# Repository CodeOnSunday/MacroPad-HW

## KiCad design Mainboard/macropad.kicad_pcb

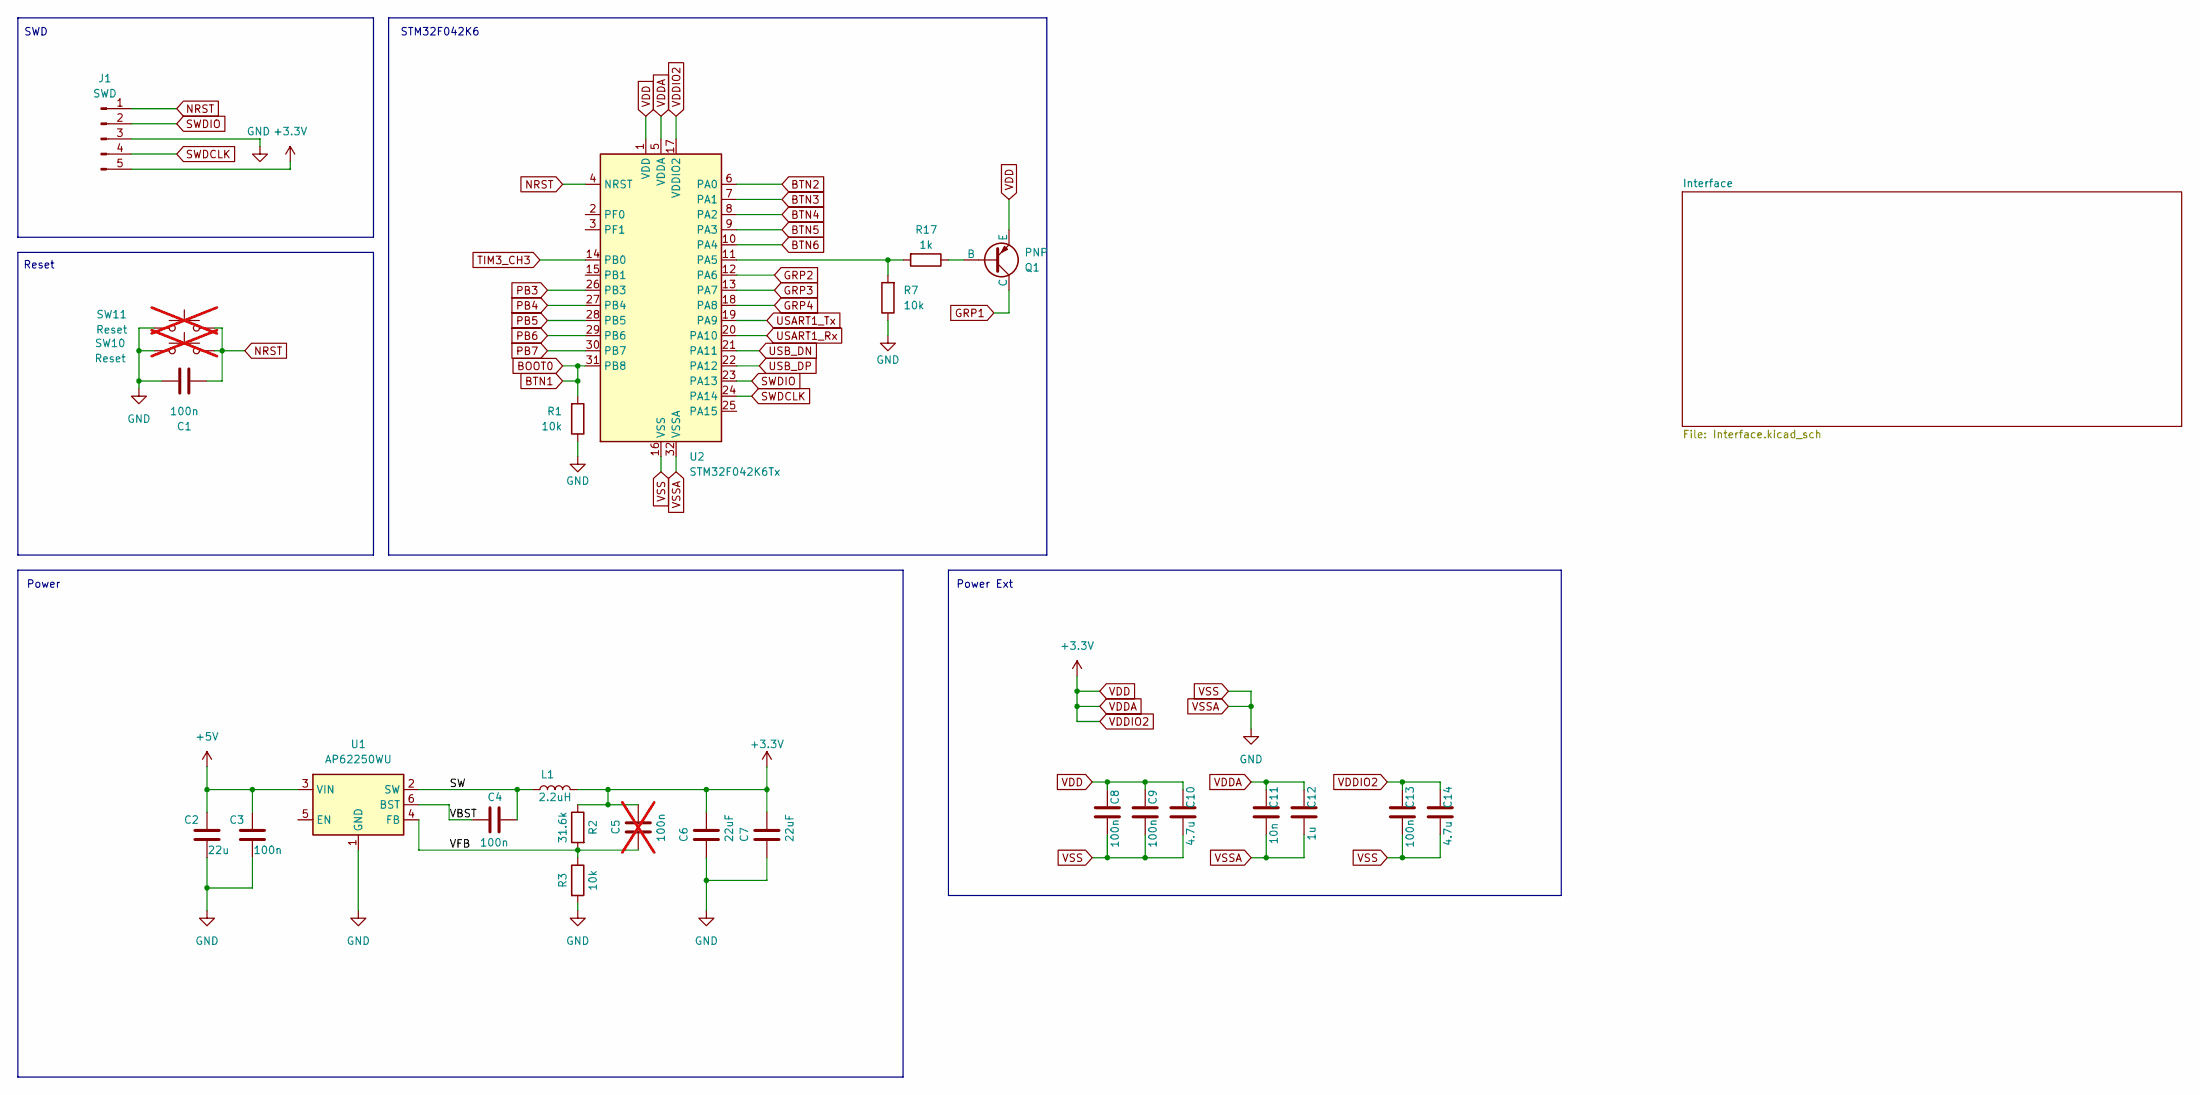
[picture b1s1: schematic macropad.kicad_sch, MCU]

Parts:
C1, C3, C4, C8, C9, C13: 100n; C_0603_1608Metric
C2: 22u; C_1206_3216Metric
C5: 100n; C_0603_1608Metric; not fitted
C6, C7: 22uF; C_1206_3216Metric
C10, C14: 4.7u; C_1206_3216Metric
C11: 10n; C_0603_1608Metric
C12: 1u; C_1206_3216Metric
J1: SWD; Conn_Edge_x05
L1: 2.2uH; L_Taiyo-Yuden_NR-50xx
Q1: PNP; SOT-23
R1, R7: 10k; R_0805_2012Metric_Pad1.20x1.40mm_HandSolder
R2: 31.6k; R_0603_1608Metric
R3: 10k; R_0603_1608Metric
R17: 1k; R_0805_2012Metric_Pad1.20x1.40mm_HandSolder
SW10, SW11: Reset; SW_SPST_B3U-1000P; not fitted
U1: AP62250WU; TSOT-23-6
U2: STM32F042K6Tx; LQFP-32_7x7mm_P0.8mm

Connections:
+5V: C2.1, C3.1, U1.3 (VIN); also elsewhere on the board
/SW: C4.1, L1.1, U1.2 (SW)
/VBST: C4.2, U1.6 (BST)
/VFB: C5.2, R2.2, R3.1, U1.4 (FB)
BOOT0: R1.2, U2.31 (PB8); also elsewhere on the board
BTN2: U2.6 (PA0); also elsewhere on the board
BTN3: U2.7 (PA1); also elsewhere on the board
BTN4: U2.8 (PA2); also elsewhere on the board
BTN5: U2.9 (PA3); also elsewhere on the board
BTN6: U2.10 (PA4); also elsewhere on the board
GRP1: Q1.1 (C); also elsewhere on the board
GRP2: U2.12 (PA6); also elsewhere on the board
GRP3: U2.13 (PA7); also elsewhere on the board
GRP4: U2.18 (PA8); also elsewhere on the board
NRST: C1.1, J1.1, SW10.2, SW11.2, U2.4 (NRST)
unnamed: Q1.2 (B), R17.1
unnamed: R7.2, R17.2, U2.11 (PA5)
PB3: U2.26 (PB3); also elsewhere on the board
PB4: U2.27 (PB4); also elsewhere on the board
PB5: U2.28 (PB5); also elsewhere on the board
PB6: U2.29 (PB6); also elsewhere on the board
PB7: U2.30 (PB7); also elsewhere on the board
SWDCLK: J1.4, U2.24 (PA14)
SWDIO: J1.2, U2.23 (PA13)
TIM3_CH3: U2.14 (PB0); also elsewhere on the board
USART1_Rx: U2.20 (PA10); also elsewhere on the board
USART1_Tx: U2.19 (PA9); also elsewhere on the board
USB_DN: U2.21 (PA11); also elsewhere on the board
USB_DP: U2.22 (PA12); also elsewhere on the board
VDD: C5.1, C6.1, C7.1, C8.2, C9.2, C10.2, C11.2, C12.2, C13.2, C14.2, J1.5, L1.2, Q1.3 (E), R2.1, U2.1 (VDD), U2.5 (VDDA), U2.17 (VDDIO2); also elsewhere on the board
VSS: C1.2, C2.2, C3.2, C6.2, C7.2, C8.1, C9.1, C10.1, C11.1, C12.1, C13.1, C14.1, J1.3, R1.1, R3.2, R7.1, SW10.1, SW11.1, U1.1 (GND), U2.16 (VSS), U2.32 (VSSA); also elsewhere on the board

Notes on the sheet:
Power Ext
Power
STM32F042K6
Reset
SWD

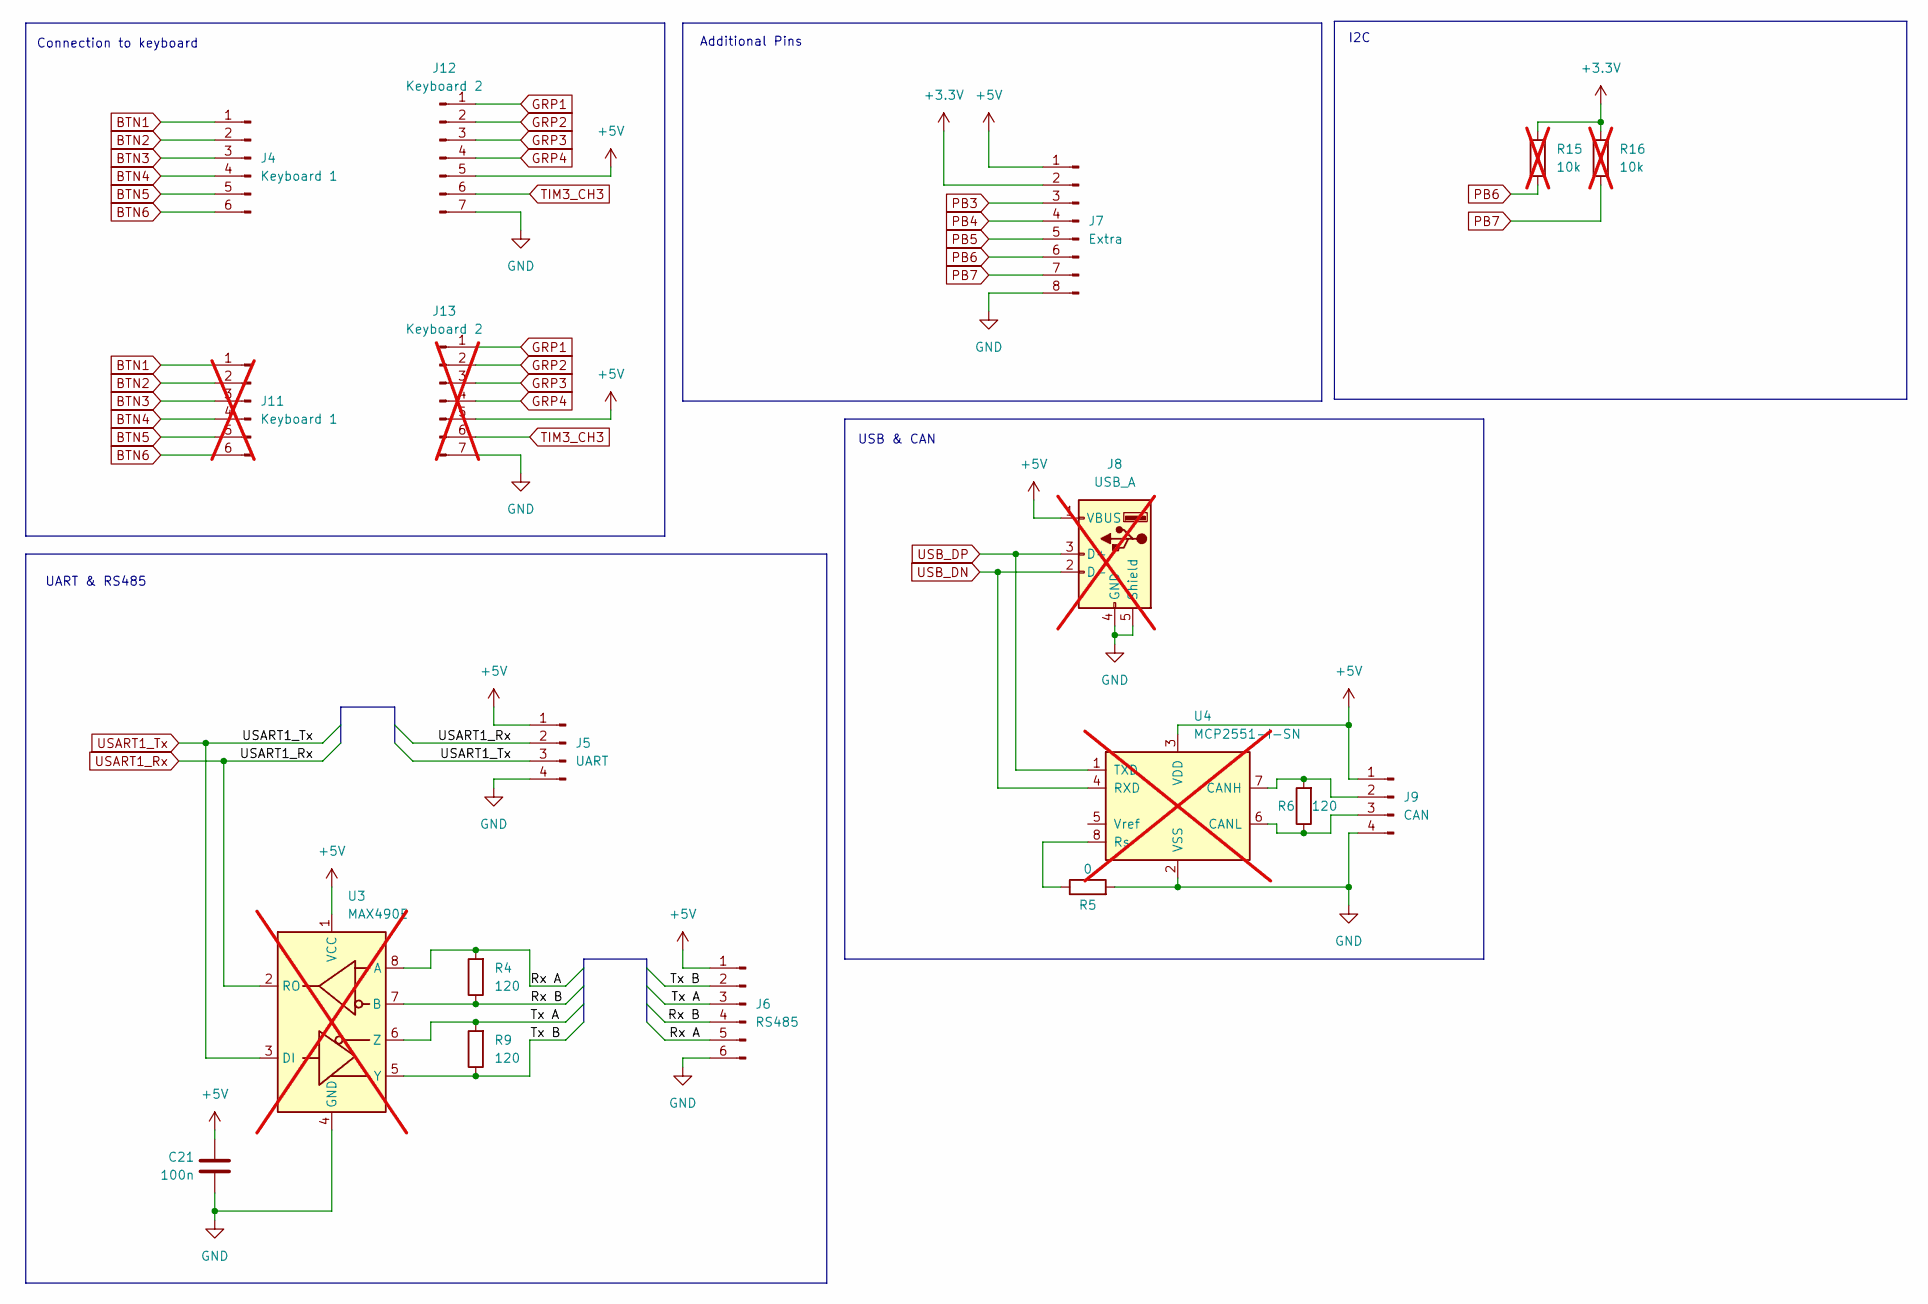
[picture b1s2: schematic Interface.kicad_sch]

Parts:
C21: 100n; C_0603_1608Metric
J4: Keyboard 1; PinHeader_1x06_P2.54mm_Vertical_SMD_Pin1Left
J5: UART; Conn_Edge_x04
J6: RS485; Conn_Edge_x06
J7: Extra; Conn_Edge_x08
J8: USB_A; USB_Micro-B_Wuerth_629105150521_CircularHoles; not fitted
J9: CAN; Conn_Edge_x04
J11: Keyboard 1; PinHeader_1x06_P2.54mm_Vertical; not fitted
J12: Keyboard 2; PinHeader_1x07_P2.54mm_Vertical_SMD_Pin1Left
J13: Keyboard 2; PinHeader_1x07_P2.54mm_Vertical; not fitted
R4, R6, R9: 120; R_0805_2012Metric_Pad1.20x1.40mm_HandSolder
R5: 0; R_0603_1608Metric
R15, R16: 10k; R_0805_2012Metric_Pad1.20x1.40mm_HandSolder; not fitted
U3: MAX490E; SOIC-8_3.9x4.9mm_P1.27mm; not fitted
U4: MCP2551-I-SN; SOIC-8_3.9x4.9mm_P1.27mm; not fitted

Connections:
+5V: C21.1, J5.1, J6.1, J7.1, J8.1 (VBUS), J9.1, J12.5, J13.5, U3.1 (VCC), U4.3 (VDD); also elsewhere on the board
/Interface/Rx A: J6.5, R4.2, U3.8 (A)
/Interface/Rx B: J6.4, R4.1, U3.7 (B)
/Interface/Tx A: J6.3, R9.2, U3.6 (Z)
/Interface/Tx B: J6.2, R9.1, U3.5 (Y)
BOOT0: J4.1, J11.1; also elsewhere on the board
BTN2: J4.2, J11.2; also elsewhere on the board
BTN3: J4.3, J11.3; also elsewhere on the board
BTN4: J4.4, J11.4; also elsewhere on the board
BTN5: J4.5, J11.5; also elsewhere on the board
BTN6: J4.6, J11.6; also elsewhere on the board
GRP1: J12.1, J13.1; also elsewhere on the board
GRP2: J12.2, J13.2; also elsewhere on the board
GRP3: J12.3, J13.3; also elsewhere on the board
GRP4: J12.4, J13.4; also elsewhere on the board
unnamed: J9.2, R6.2, U4.7 (CANH)
unnamed: J9.3, R6.1, U4.6 (CANL)
unnamed: R5.1, U4.8 (Rs)
PB3: J7.3; also elsewhere on the board
PB4: J7.4; also elsewhere on the board
PB5: J7.5; also elsewhere on the board
PB6: J7.6, R15.1; also elsewhere on the board
PB7: J7.7, R16.1; also elsewhere on the board
TIM3_CH3: J12.6, J13.6; also elsewhere on the board
USART1_Rx: J5.2, U3.2 (RO); also elsewhere on the board
USART1_Tx: J5.3, U3.3 (DI); also elsewhere on the board
USB_DN: J8.2 (D-), U4.4 (RXD); also elsewhere on the board
USB_DP: J8.3 (D+), U4.1 (TXD); also elsewhere on the board
VDD: J7.2, R15.2, R16.2; also elsewhere on the board
VSS: C21.2, J5.4, J6.6, J7.8, J8.4 (GND), J8.5 (Shield), J9.4, J12.7, J13.7, R5.2, U3.4 (GND), U4.2 (VSS); also elsewhere on the board

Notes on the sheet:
I2C
Additional Pins
UART & RS485
USB & CAN
Connection to keyboard

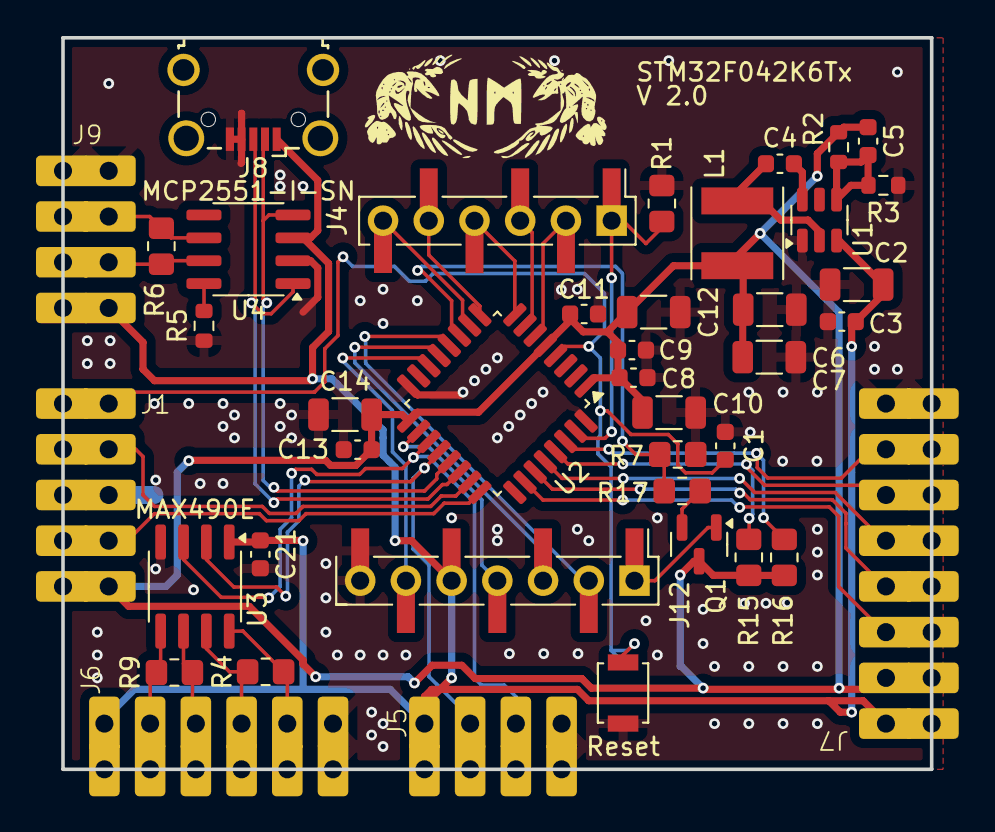
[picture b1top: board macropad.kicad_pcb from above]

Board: 2 copper layers, 48.3 x 40.6 mm, 44 parts (1 on the bottom side), 38 nets.

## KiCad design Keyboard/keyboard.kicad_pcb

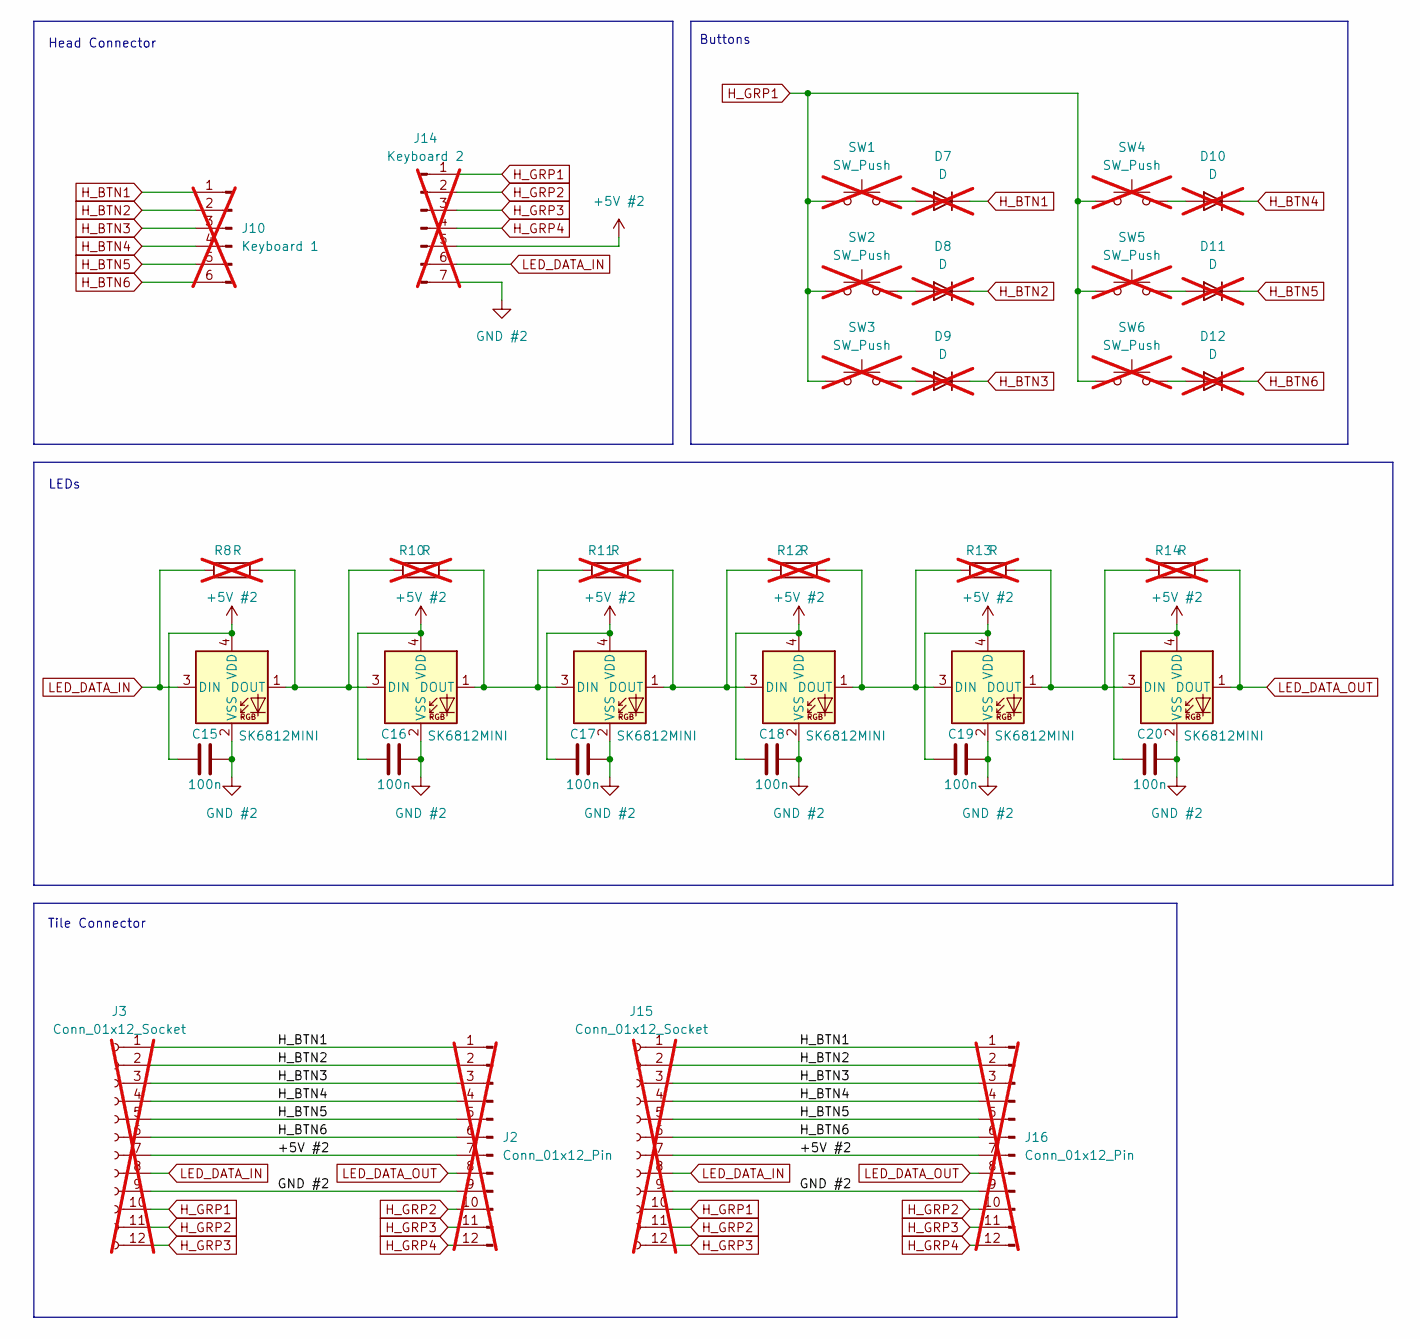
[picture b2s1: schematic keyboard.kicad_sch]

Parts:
C15, C16, C17, C18, C19, C20: 100n; C_0603_1608Metric
D1, D2, D3, D4, D5, D6: SK6812MINI; LED_SK6812MINI_PLCC4_3.5x3.5mm_P1.75mm
D7, D8, D9, D10, D11, D12: D; D_0603_1608Metric; not fitted
J2, J16: Conn_01x12_Pin; PinHeader_1x12_P2.54mm_Horizontal; not fitted
J3, J15: Conn_01x12_Socket; PinSocket_1x12_P2.54mm_Horizontal; not fitted
J10: Keyboard 1; PinHeader_1x06_P2.54mm_Vertical; not fitted
J14: Keyboard 2; PinHeader_1x07_P2.54mm_Vertical; not fitted
R8, R10, R11, R12, R13, R14: R; R_0603_1608Metric; not fitted
SW1, SW2, SW3, SW4, SW5, SW6: SW_Push; Gateron Pro; not fitted

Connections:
+5V #2: C15.2, C16.2, C17.2, C18.2, C19.2, C20.2, D1.4 (VDD), D2.4 (VDD), D3.4 (VDD), D4.4 (VDD), D5.4 (VDD), D6.4 (VDD), J2.7, J3.7, J14.5, J15.7, J16.7
GND #2: C15.1, C16.1, C17.1, C18.1, C19.1, C20.1, D1.2 (VSS), D2.2 (VSS), D3.2 (VSS), D4.2 (VSS), D5.2 (VSS), D6.2 (VSS), J2.9, J3.9, J14.7, J15.9, J16.9
H_BTN1: D7.1 (K), J2.1, J3.1, J10.1, J15.1, J16.1
H_BTN2: D8.1 (K), J2.2, J3.2, J10.2, J15.2, J16.2
H_BTN3: D9.1 (K), J2.3, J3.3, J10.3, J15.3, J16.3
H_BTN4: D10.1 (K), J2.4, J3.4, J10.4, J15.4, J16.4
H_BTN5: D11.1 (K), J2.5, J3.5, J10.5, J15.5, J16.5
H_BTN6: D12.1 (K), J2.6, J3.6, J10.6, J15.6, J16.6
H_GRP1: J3.10, J14.1, J15.10, SW1.1, SW2.1, SW3.1, SW4.1, SW5.1, SW6.1
H_GRP2: J2.10, J3.11, J14.2, J15.11, J16.10
H_GRP3: J2.11, J3.12, J14.3, J15.12, J16.11
H_GRP4: J2.12, J14.4, J16.12
LED_DATA_IN: D1.3 (DIN), J3.8, J14.6, J15.8, R8.1
LED_DATA_OUT: D6.1 (DOUT), J2.8, J16.8, R14.2
unnamed: D1.1 (DOUT), D2.3 (DIN), R8.2, R10.1
unnamed: D2.1 (DOUT), D3.3 (DIN), R10.2, R11.1
unnamed: D3.1 (DOUT), D4.3 (DIN), R11.2, R12.1
unnamed: D4.1 (DOUT), D5.3 (DIN), R12.2, R13.1
unnamed: D5.1 (DOUT), D6.3 (DIN), R13.2, R14.1
unnamed: D7.2 (A), SW1.2
unnamed: D8.2 (A), SW2.2
unnamed: D9.2 (A), SW3.2
unnamed: D10.2 (A), SW4.2
unnamed: D11.2 (A), SW5.2
unnamed: D12.2 (A), SW6.2

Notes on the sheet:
Head Connector
LEDs
Tile Connector
Buttons

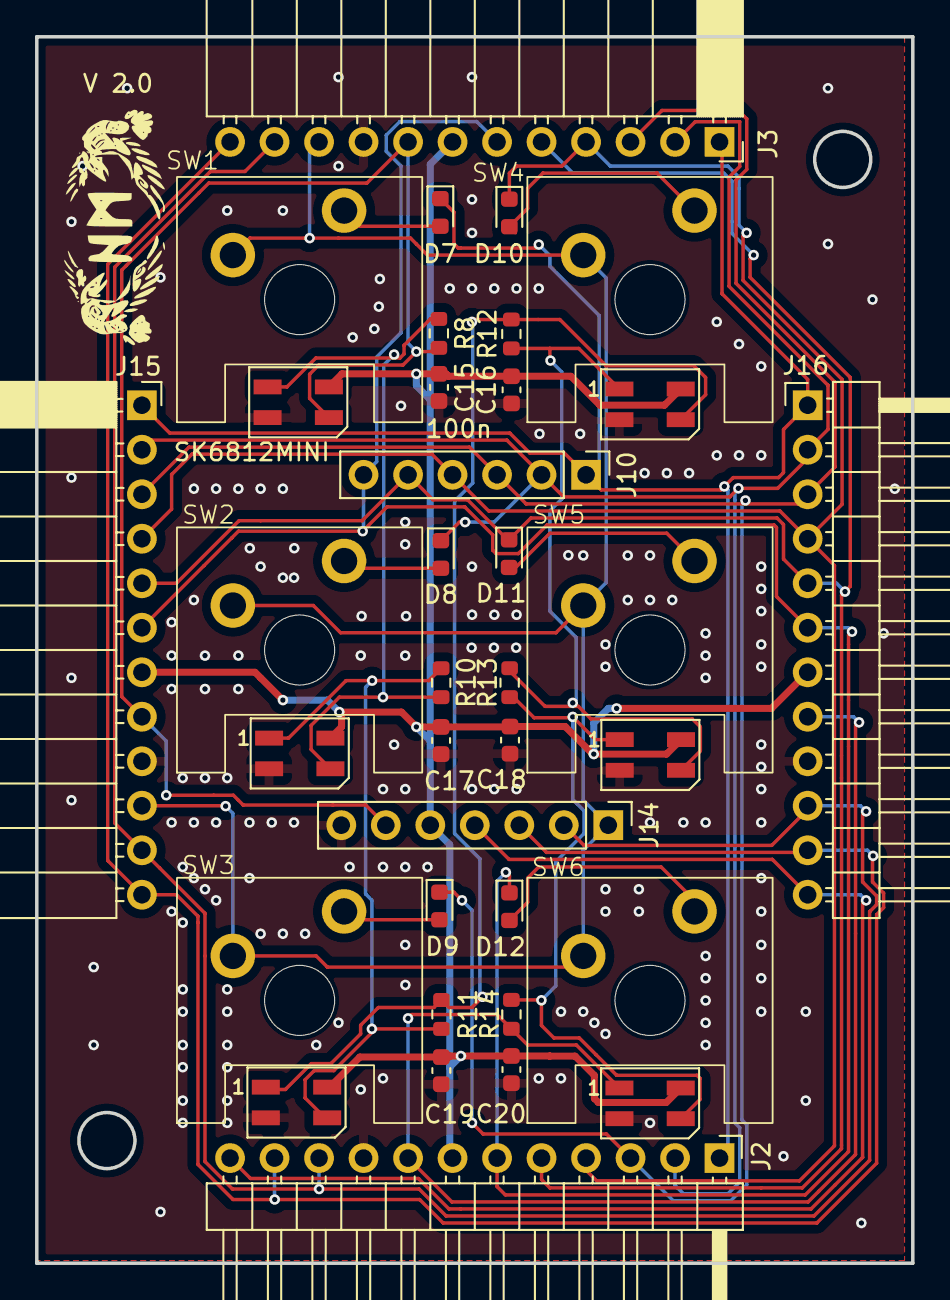
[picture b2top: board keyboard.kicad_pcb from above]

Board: 2 copper layers, 50.0 x 70.0 mm, 36 parts (0 on the bottom side), 25 nets.

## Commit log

2025-04-15 Version 1.0 Initial commit
2025-04-15 - Created head board tilable up to 4x - Placed and routed lines ToDo: - Print - I2C reanbable
2025-04-16 - Silkscreen positions fixed
2025-04-16 - Added Pull Ups for I2C - Added second reset button on bottom side
2025-04-16 - fixed error in transistor circuit - fixed orientation of silkscreen text - DRC: Okay
2025-04-16 - Moved component name to silkscreen - Added version notation to boards
2025-04-18 - Added JLC plugin database
2025-04-18 - Added missing library files to git - Added logo to silkscreen - ERC: Okay
2025-04-20 Separated Keyboard schematic and pcb to a separate project in the same folder.
2025-05-13 Cleaned up project structure.
2025-05-13 Fixed wrong library paths after moving the project to subfolders.
